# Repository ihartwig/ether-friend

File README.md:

# ether-friend
Custom-purpose and hackable ethernet adapters

[papoe-pi-zero](papoe-pi-zero) Pi Zero HAT with FRC-compatible passive PoE 100M usb-ethernet adapter

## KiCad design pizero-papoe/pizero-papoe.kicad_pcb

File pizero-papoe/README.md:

Pi Zero PaPoE HAT
=================

1GBASE-T ethernet HAT for Pi Zero v1.3, Zero W v 1.1, and Zero 2W using the RTL8153B controller. Also includes a USB C plug to carry USB 3 signals.

### Examples of RTL8153/RTL8153B Implementation
Since the reference schematic from Realtek is not generally available for the RTL8153 part and there are somefeatures requiring specific external components such as the switch regulator, this design borrows from the following schematics:
https://dn.odroid.com/5422/ODROID-XU3/Schematics/XU4_MAIN_REV0.1.pdf
https://www.96boards.org/documentation/consumer/dragonboard/db4/hardware-docs/files/db4-sch.pdf
https://github.com/OLIMEX/USB-GIGABIT/blob/master/HARDWARE/USB-GIGABIT-Rev.C/USB-GIGABIT_Rev_C.pdf

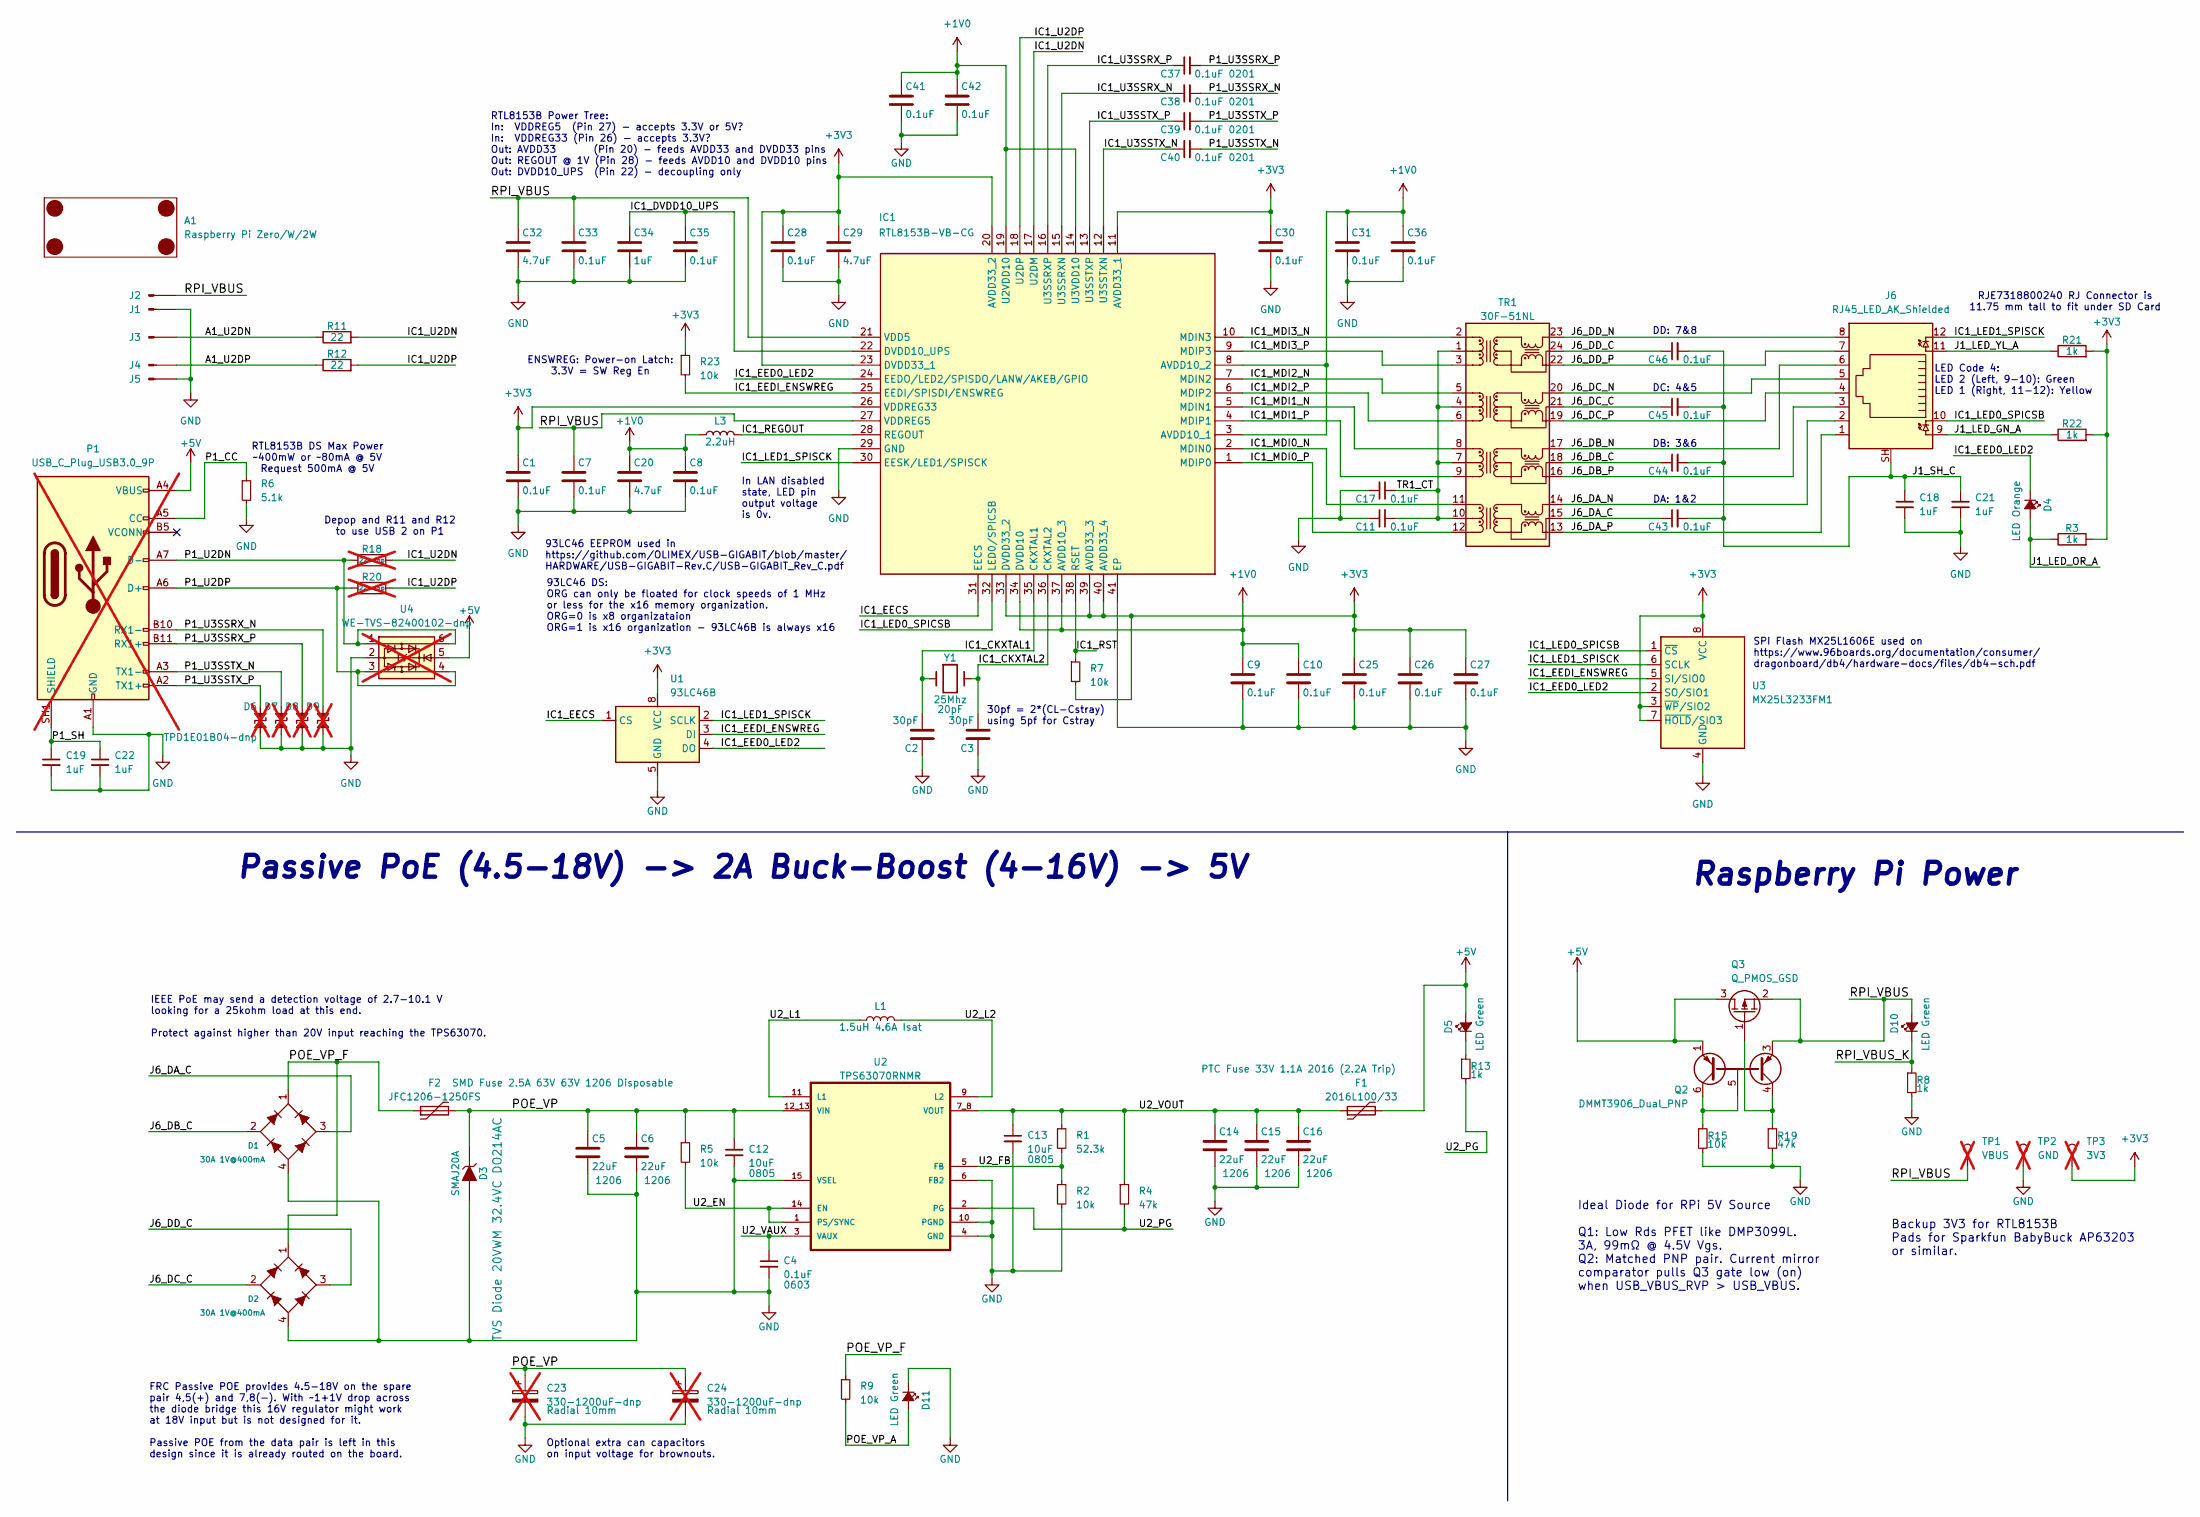
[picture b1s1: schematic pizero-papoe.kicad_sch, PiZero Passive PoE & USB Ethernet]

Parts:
A1: Raspberry Pi Zero/W/2W; RPi_Zero_ZeroW_Zero2W_Hat_NoPads_NoHeader; LCSC --
C1, C7, C8, C9, C10, C11, C17, C25, C26, C27, C28, C30, C31, C33, C35, C36, C41, C42, C43, C44, C45, C46: 0.1uF; C_0603_1608Metric; LCSC C6119867
C2: 30pF; C_0603_1608Metric; Mfg PN 0603CG300F500NT; LCSC C501847
C3: 30pF; C_0603_1608Metric; LCSC C501847
C4: 0.1uF; C_0603_1608Metric; Mfg Part No CC0603KRX7R7BB104; LCSC C6119867
C5: 22uF; C_1206_3216Metric; Mfg Part No CC1206KKX5R8BB226; LCSC C6119965
C6, C14, C15, C16: 22uF; C_1206_3216Metric; LCSC C6119965
C12: 10uF; C_0805_2012Metric; Mfg Part No GRT21BC71E106KE13L; LCSC C882505
C13: 10uF; C_0805_2012Metric; LCSC C882505
C18, C19, C21, C22, C34: 1uF; C_0603_1608Metric; LCSC C5673
C20, C29, C32: 4.7uF; C_0603_1608Metric; LCSC C6119855
C23, C24: 330-1200uF-dnp; CP_Radial_D10.0mm_P5.00mm; Mfg Part No RNL1E122MDSASQ; not fitted
C37, C38, C39, C40: 0.1uF 0201; C_0201_0603Metric; LCSC C6119757
D1: 30A 1V@400mA; MBS; Mfg Part No HD01-T; Digikey Part No HD01DICT-ND
D2: 30A 1V@400mA; MBS; LCSC C2488
D3: SMAJ20A; D_SMA; Mfg Part No SMAJ20A; LCSC C115250
D4: LED Orange; LED_0603_1608Metric; Mfg Part No LTST-C190KFKT; LCSC C157740
D5, D10, D11: LED Green; LED_0603_1608Metric; Mfg Part No LTST-C190GKT; LCSC C125093
D6: TPD1E01B04-dnp; D_0402_1005Metric; Mfg PN TPD1E01B04DPYR; LCSC C779389; not fitted
D7, D8, D9: TPD1E01B04-dnp; D_0402_1005Metric; LCSC C779389; not fitted
F1: 2016L100/33; Fuse_2016_5041Metric; Mfg Part No 2016L100/33DR; LCSC C207077
F2: JFC1206-1250FS; Fuse_1206_3216Metric; Mfg Part No JFC1206-1250FS; LCSC C136346
IC1: RTL8153B-VB-CG; QFN-40-1EP_5x5mm_P0.4mm_EP3.6x3.6mm_ThermalVias; Mfg PN RTL8153B-VB-CG; LCSC C2802072
J1, J2, J3, J4, J5: PogoPin_01x01; PogoPin_CPG-01-TH-TR; Mfg PN CPG-01-TH-B; LCSC --
J6: RJ45_LED_AK_Shielded; RJ45_Amphenol_RJE7318800xxx0x; Mfg PN RJE7318800240; LCSC --
L1: 1.5uH 4.6A Isat; L_Sunlord_SWPA4030S; Mfg Part No XFL4020-152ME; LCSC C5127390
L3: 2.2uH; L_1008_2520Metric; Mfg Part No SFE252010S-2R2M-HF; LCSC C2986800
P1: USB_C_Plug_USB3.0_9P; USB_C_Plug_G-Switch_GT-USB-8016A_9P_TopMnt_Horizontal; Mfg PN GT-USB-8016A; not fitted
Q2: DMMT3906_Dual_PNP; SOT-23-6; Mfg Part No DMMT3906-7-F; Digikey Part No DMMT3906-7-FDICT-ND
Q3: Q_PMOS_GSD; SOT-23; Mfg Part No DMP3099L-7; Digikey Part No DMP3099L-7DICT-ND
R1: 52.3k; R_0603_1608Metric; LCSC C23198
R2, R5, R7, R9, R15, R23: 10k; R_0603_1608Metric; LCSC C15401
R3, R8, R13, R21, R22: 1k; R_0603_1608Metric; LCSC C21190
R4, R19: 47k; R_0603_1608Metric; LCSC C25600
R6: 5.1k; R_0603_1608Metric; LCSC C26000
R11, R12: 22; R_0603_1608Metric; LCSC C1203
R18, R20: 22-dnp; R_0603_1608Metric; not fitted
TP1: VBUS; TestPoint_Pad_D1.5mm; not fitted
TP2: GND; TestPoint_Pad_D1.5mm; not fitted
TP3: 3V3; TestPoint_Pad_D1.5mm; not fitted
TR1: 30F-51NL; Transformer_Ethernet_YDS_30F-51NL_SO-24_7.1x15.1mm; LCSC C123168
U1: 93LC46B; SOIC-8_3.9x4.9mm_P1.27mm; Mfg Pn 93LC46B/SN; LCSC C1348804
U2: TPS63070RNMR; VREG_TPS63070RNMR; Mfg Part No TPS63070RNMR; LCSC C109322
U3: MX25L3233FM1; SOP-8_5.28x5.23mm_P1.27mm; Mfg PN MX25L1606EM2I-12G; LCSC C415878
U4: WE-TVS-82400102-dnp; SOT-23-6; not fitted
Y1: 25Mhz; Crystal_SMD_5032-2Pin_5.0x3.2mm; Mfg Part No 445I23D25M00000; Digikey Part No CTX1175CT-ND

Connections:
+1V0: C8.1, C9.1, C10.1, C20.1, C31.1, C36.1, C41.1, C42.1, IC1.3 (AVDD10_1), IC1.8 (AVDD10_2), IC1.14 (U3VDD10), IC1.19 (U2VDD10), IC1.34 (DVDD10), IC1.37 (AVDD10_3), L3.1
+3V3: C1.1, C25.1, C26.1, C27.1, C28.1, C29.1, C30.1, IC1.11 (AVDD33_1), IC1.20 (AVDD33_2), IC1.23 (DVDD33_1), IC1.26 (VDDREG33), IC1.33 (DVDD33_2), IC1.39 (AVDD33_3), IC1.40 (AVDD33_4), R3.2, R7.2, R21.2, R22.2, R23.1, TP3.1, U1.8 (VCC), U3.3 (~WP/SIO2), U3.7 (~HOLD/SIO3), U3.8 (VCC)
+5V: D5.2 (A), F1.2, P1.A4 (VBUS), P1.A9 (VBUS), P1.B4 (VBUS), P1.B9 (VBUS), Q2.1 (E1), Q3.3 (D), U4.5
/A1_U2DN: J3.1, R11.1
/A1_U2DP: J4.1, R12.1
/IC1_CKXTAL1: C2.2, IC1.35 (CKXTAL1), Y1.1
/IC1_CKXTAL2: C3.2, IC1.36 (CKXTAL2), Y1.2
/IC1_DVDD10_UPS: C34.1, C35.1, IC1.22 (DVDD10_UPS)
/IC1_EECS: IC1.31 (EECS), U1.1 (CS)
/IC1_EED0_LED2: D4.1 (K), IC1.24 (EEDO/LED2/SPISDO/LANW/AKEB/GPIO), U1.4 (DO), U3.2 (SO/SIO1)
/IC1_EEDI_ENSWREG: IC1.25 (EEDI/SPISDI/ENSWREG), R23.2, U1.3 (DI), U3.5 (SI/SIO0)
/IC1_LED0_SPICSB: IC1.32 (LED0/SPICSB), J6.10, U3.1 (~CS)
/IC1_LED1_SPISCK: IC1.30 (EESK/LED1/SPISCK), J6.12, U1.2 (SCLK), U3.6 (SCLK)
/IC1_MDI0_N: IC1.2 (MDIN0), TR1.11 (TD4+)
/IC1_MDI0_P: IC1.1 (MDIP0), TR1.12 (TD4-)
/IC1_MDI1_N: IC1.5 (MDIN1), TR1.8 (TD3+)
/IC1_MDI1_P: IC1.4 (MDIP1), TR1.9 (TD3-)
/IC1_MDI2_N: IC1.7 (MDIN2), TR1.5 (TD2+)
/IC1_MDI2_P: IC1.6 (MDIP2), TR1.6 (TD2-)
/IC1_MDI3_N: IC1.10 (MDIN3), TR1.2 (TD1+)
/IC1_MDI3_P: IC1.9 (MDIP3), TR1.3 (TD1-)
/IC1_REGOUT: IC1.28 (REGOUT), L3.2
/IC1_RST: IC1.38 (RSET), R7.1
/IC1_U2DN: IC1.17 (U2DM), R11.2, R18.2
/IC1_U2DP: IC1.18 (U2DP), R12.2, R20.2
/IC1_U3SSRX_N: C38.1, IC1.15 (U3SSRXN)
/IC1_U3SSRX_P: C37.1, IC1.16 (U3SSRXP)
/IC1_U3SSTX_N: C40.1, IC1.12 (U3SSTXN)
/IC1_U3SSTX_P: C39.1, IC1.13 (U3SSTXP)
/J1_LED_GN_A: J6.9, R22.1
/J1_LED_OR_A: D4.2 (A), R3.1
/J1_LED_YL_A: J6.11, R21.1
/J1_SH_C: C18.1, C21.1, C43.2, C44.2, C45.2, C46.2, J6.SH
/J6_DA_C: C43.1, D1.3 (~2), TR1.15 (CT)
/J6_DA_N: J6.2, TR1.14 (MX4+)
/J6_DA_P: J6.1, TR1.13 (MX4-)
/J6_DB_C: C44.1, D1.2 (~1), TR1.18 (CT)
/J6_DB_N: J6.6, TR1.17 (MX3+)
/J6_DB_P: J6.3, TR1.16 (MX3-)
/J6_DC_C: C45.1, D2.2 (~1), TR1.21 (CT)
/J6_DC_N: J6.5, TR1.20 (MX2+)
/J6_DC_P: J6.4, TR1.19 (MX2-)
/J6_DD_C: C46.1, D2.3 (~2), TR1.24 (CT)
/J6_DD_N: J6.8, TR1.23 (MX1+)
/J6_DD_P: J6.7, TR1.22 (MX1-)
/P1_CC: P1.A5 (CC), R6.1
/P1_SH: C19.1, C22.1, P1.SH1 (SHIELD)
/P1_U2DN: P1.A7 (D-), R18.1, U4.1, U4.6
/P1_U2DP: P1.A6 (D+), R20.1, U4.3, U4.4
/P1_U3SSRX_N: C38.2, D9.1 (A1), P1.B10 (RX1-)
/P1_U3SSRX_P: C37.2, D8.1 (A1), P1.B11 (RX1+)
/P1_U3SSTX_N: C40.2, D7.1 (A1), P1.A3 (TX1-)
/P1_U3SSTX_P: C39.2, D6.1 (A1), P1.A2 (TX1+)
/POE_VP: C5.1, C6.1, C12.1, C23.1, C24.1, D3.1 (K), F2.2, R5.1, U2.12_13 (VIN)
/POE_VP_A: D11.2 (A), R9.2
/POE_VP_F: D1.1 (V+), D2.1 (V+), F2.1, R9.1
/RPI_VBUS: C7.1, C32.1, C33.1, D10.2 (A), IC1.21 (VDD5), IC1.27 (VDDREG5), J2.1, Q2.3 (E2), Q3.2 (S), TP1.1
/RPI_VBUS_K: D10.1 (K), R8.1
/TR1_CT: C11.2, C17.2, TR1.1 (CT), TR1.4 (CT), TR1.7 (CT), TR1.10 (CT)
/U2_EN: R5.2, U2.1 (PS/SYNC), U2.14 (EN)
/U2_FB: R1.2, R2.1, U2.5 (FB)
/U2_L1: L1.1, U2.11 (L1)
/U2_L2: L1.2, U2.9 (L2)
/U2_PG: R4.2, R13.2, U2.2 (PG)
/U2_VAUX: C4.1, U2.3 (VAUX)
/U2_VOUT: C13.1, C14.1, C15.1, C16.1, F1.1, R1.1, R4.1, U2.7_8 (VOUT)
GND: C1.2, C2.1, C3.1, C4.2, C5.2, C6.2, C7.2, C8.2, C9.2, C10.2, C11.1, C12.2, C13.2, C14.2, C15.2, C16.2, C17.1, C18.2, C19.2, C20.2, C21.2, C22.2, C23.2, C24.2, C25.2, C26.2, C27.2, C28.2, C29.2, C30.2, C31.2, C32.2, C33.2, C34.2, C35.2, C36.2, C41.2, C42.2, D1.4 (V-), D2.4 (V-), D3.2 (A), D6.2 (A2), D7.2 (A2), D8.2 (A2), D9.2 (A2), D11.1 (K), IC1.29 (GND), IC1.41 (EP), J1.1, J5.1, P1.A1 (GND), P1.A12 (GND), P1.B1 (GND), P1.B12 (GND), R2.2, R6.2, R8.2, R15.2, R19.2, TP2.1, U1.5 (GND), U2.4 (GND), U2.6 (FB2), U2.10 (PGND), U2.15 (VSEL), U3.4 (GND), U4.2
unnamed: D5.1 (K), R13.1
unnamed: Q2.5 (B), Q2.6 (C1), R15.1
unnamed: Q2.4 (C2), Q3.1 (G), R19.1

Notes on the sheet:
DC: 4&5
Depop and R11 and R12 to use USB 2 on P1
RTL8153B Power Tree: In: VDDREG5 (Pin 27) - accepts 3.3V or 5V? In: VDDREG33 (Pin 26) - accepts 3.3V? Out: AVDD33 (Pin 20) - feeds AVDD33 and DVDD33 pins Out: REGOUT @ 1V (Pin 28) - feeds AVDD10 and DVDD10 pins Out: DVDD10_UPS (Pin 22) - decoupling only
IEEE PoE may send a detection voltage of 2.7-10.1 V looking for a 25kohm load at this end. Protect against higher than 20V input reaching the TPS63070.
RTL8153B DS Max Power ~400mW or ~80mA @ 5V Request 500mA @ 5V
RJE7318800240 RJ Connector is 11.75 mm tall to fit under SD Card
ENSWREG: Power-on Latch: 3.3V = SW Reg En
Passive PoE (4.5-18V) -> 2A Buck-Boost (4-16V) -> 5V
In LAN disabled state, LED pin output voltage is 0v.
30pf = 2*(CL-Cstray) using 5pf for Cstray
DD: 7&8
Raspberry Pi Power
SPI Flash MX25L1606E used on https://www.96boards.org/documentation/consumer/ dragonboard/db4/hardware-docs/files/db4-sch.pdf
Ideal Diode for RPi 5V Source Q1: Low Rds PFET like DMP3099L. 3A, 99mΩ @ 4.5V Vgs. Q2: Matched PNP pair. Current mirror comparator pulls Q3 gate low (on) when USB_VBUS_RVP > USB_VBUS.
DA: 1&2
DB: 3&6
93LC46 EEPROM used in https://github.com/OLIMEX/USB-GIGABIT/blob/master/ HARDWARE/USB-GIGABIT-Rev.C/USB-GIGABIT_Rev_C.pdf
Backup 3V3 for RTL8153B Pads for Sparkfun BabyBuck AP63203 or similar.
FRC Passive POE provides 4.5-18V on the spare pair 4,5(+) and 7,8(-). With ~1+1V drop across the diode bridge this 16V regulator might work at 18V input but is not designed for it. Passive POE from the data pair is left in this design since it is already routed on the board.
93LC46 DS: ORG can only be floated for clock speeds of 1 MHz or less for the x16 memory organization. ORG=0 is x8 organizataion ORG=1 is x16 organization - 93LC46B is always x16
Optional extra can capacitors on input voltage for brownouts.
LED Code 4: LED 2 (Left, 9-10): Green LED 1 (Right, 11-12): Yellow

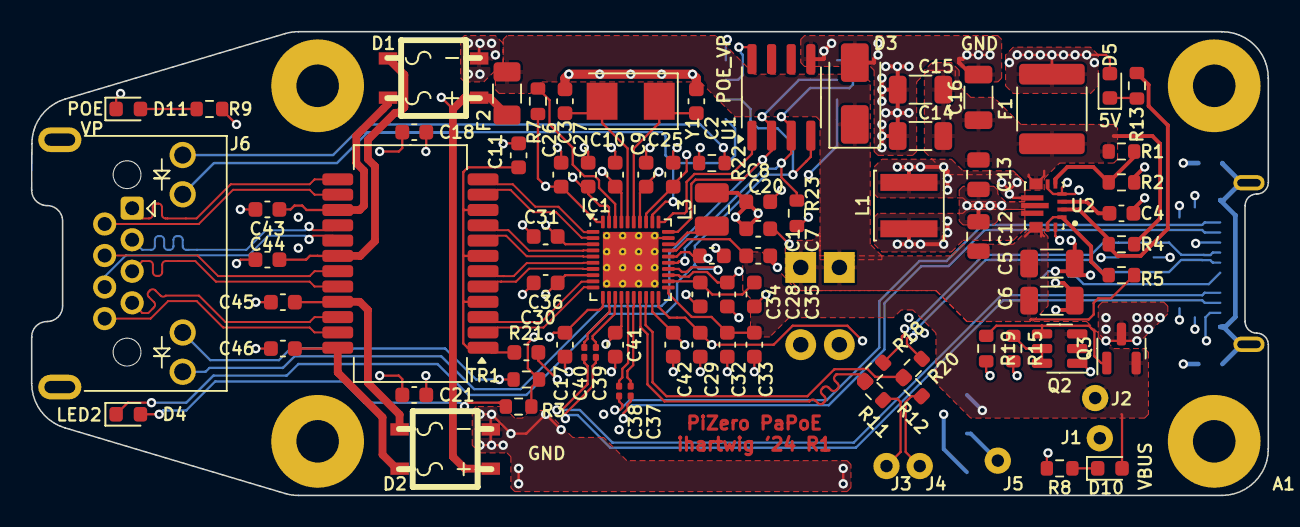
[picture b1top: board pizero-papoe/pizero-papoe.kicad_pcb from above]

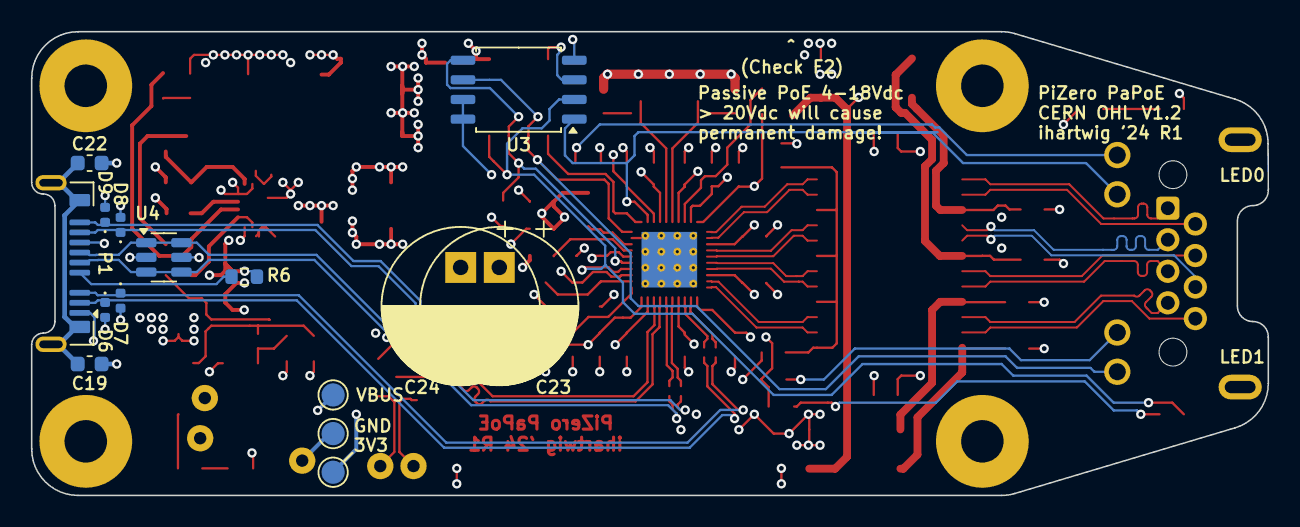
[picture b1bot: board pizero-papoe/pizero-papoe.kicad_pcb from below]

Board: 4 copper layers, 80.0 x 30.0 mm, 100 parts (15 on the bottom side), 70 nets.

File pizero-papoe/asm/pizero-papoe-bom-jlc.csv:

"Designator","Footprint","Qty","DNP","LCSC","Comment","Description"
"A1","Raspberry_Pi_Zero_v.1.3_Hat:RPi_Zero_ZeroW_Zero2W_Hat_NoPads_NoHeader","1","","--","Raspberry Pi Zero/W/2W","Raspberry Pi Zero v1.3"
"C1,C4,C7,C8,C9,C10,C11,C17,C25,C26,C27,C28,C30,C31,C33,C35,C36,C41,C42,C43,C44,C45,C46","Capacitor_SMD:C_0603_1608Metric","23","","C6119867","0.1uF","±10% 100nF 50V X7R 0603 MLCC"
"C2,C3","Capacitor_SMD:C_0603_1608Metric","2","","C501847","30pF",""
"C5,C6,C14,C15,C16","Capacitor_SMD:C_1206_3216Metric","5","","C6119965","22uF","-- mixed values --"
"C12,C13","Capacitor_SMD:C_0805_2012Metric","2","","C882505","10uF","-- mixed values --"
"C18,C19,C21,C22,C34","Capacitor_SMD:C_0603_1608Metric","5","","C5673","1uF","25V 1uF X7R ±10% 0603 MLCC"
"C20,C29,C32","Capacitor_SMD:C_0603_1608Metric","3","","C6119855","4.7uF","16V 4.7uF X5R ±10% 0603 MLCC"
"C37,C38,C39,C40","Capacitor_SMD:C_0201_0603Metric","4","","C6119757","0.1uF 0201","10V 100nF X5R ±10% 0201 MLCC"
"D1,D2","pizero-poe-special:MBS","2","","C2488","30A 1V@400mA","30A 1V@400mA 800mA 100V MBS Bridge Rectifiers ROHS"
"D3","Diode_SMD:D_SMA","1","","C115250","SMAJ20A","TVS Diode 20VWM 32.4VC DO214AC"
"D4","LED_SMD:LED_0603_1608Metric","1","","C157740","LED Orange","LED ORANGE CLEAR 0603 SMD"
"D5,D10,D11","LED_SMD:LED_0603_1608Metric","3","","C125093","LED Green","LED GREEN CLEAR 0603 SMD"
"F1","pizero-poe-special:Fuse_2016_5041Metric","1","","C207077","2016L100/33","PTC Fuse 33V 1.1A 2016 (2.2A Trip)"
"F2","Fuse:Fuse_1206_3216Metric","1","","C136346","JFC1206-1250FS","SMD Fuse 2.5A 63V 63V 1206 Disposable"
"IC1","Package_DFN_QFN:QFN-40-1EP_5x5mm_P0.4mm_EP3.6x3.6mm_ThermalVias","1","","C2802072","RTL8153B-VB-CG",""
"J1,J2,J3,J4,J5","pizero-poe-special:PogoPin_CPG-01-TH-TR","5","","--","PogoPin_01x01",""
"J6","pizero-poe-special:RJ45_Amphenol_RJE7318800xxx0x","1","","--","RJ45_LED_AK_Shielded","RJ connector, 8P8C (8 positions 8 connected), two LEDs, RJ45, Shielded"
"L1","Inductor_SMD:L_Sunlord_SWPA4030S","1","","C5127390","1.5uH 4.6A Isat","1.5uH Shielded inductor ±20% 4.84A SMD,4x4mm Power Inductors ROHS"
"L3","Inductor_SMD:L_1008_2520Metric","1","","C2986800","2.2uH","1.5A 2.2uH ±20% 1.35A 1008 Power Inductors ROHS"
"Q2","Package_TO_SOT_SMD:SOT-23-6","1","","C526572","DMMT3906_Dual_PNP","TRANS 2PNP 40V 0.2A SOT26"
"Q3","Package_TO_SOT_SMD:SOT-23","1","","C155244","Q_PMOS_GSD","MOSFET P-CH 30V SOT23"
"R1","Resistor_SMD:R_0603_1608Metric","1","","C23198","52.3k",""
"R2,R5,R7,R9,R15,R23","Resistor_SMD:R_0603_1608Metric","6","","C15401","10k",""
"R3,R8,R13,R21,R22","Resistor_SMD:R_0603_1608Metric","5","","C21190","1k",""
"R4,R19","Resistor_SMD:R_0603_1608Metric","2","","C25600","47k",""
"R6","Resistor_SMD:R_0603_1608Metric","1","","C26000","5.1k",""
"R11,R12","Resistor_SMD:R_0603_1608Metric","2","","C1203","22",""
"TR1","Transformer_SMD:Transformer_Ethernet_YDS_30F-51NL_SO-24_7.1x15.1mm","1","","C123168","30F-51NL","1CT:1CT 10/100/1000 Base-T Ethernet Transformer, SMD-24"
"U1","Package_SO:SOIC-8_3.9x4.9mm_P1.27mm","1","","C1348804","93LC46B","Serial EEPROM, 93 Series, 2.5V, DIP-8/SOIC-8"
"U2","pizero-poe-special:VREG_TPS63070RNMR","1","","C109322","TPS63070RNMR","Wide input voltage (2V-16V) buck-boost converter"
"U3","Package_SO:SOP-8_5.28x5.23mm_P1.27mm","1","","C415878","MX25L3233FM1","32-Mbit, 3V (2.65V-3.6V) SPI Serial Flash Memory, SOP-8 (150mil)"
"Y1","Crystal:Crystal_SMD_5032-2Pin_5.0x3.2mm","1","","C251592","25Mhz",""

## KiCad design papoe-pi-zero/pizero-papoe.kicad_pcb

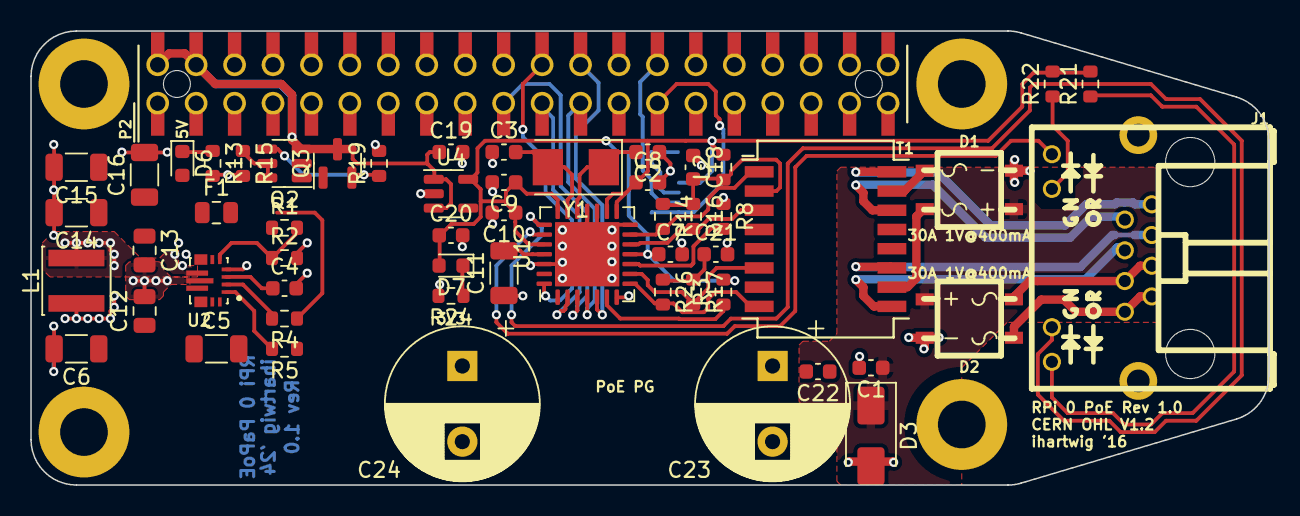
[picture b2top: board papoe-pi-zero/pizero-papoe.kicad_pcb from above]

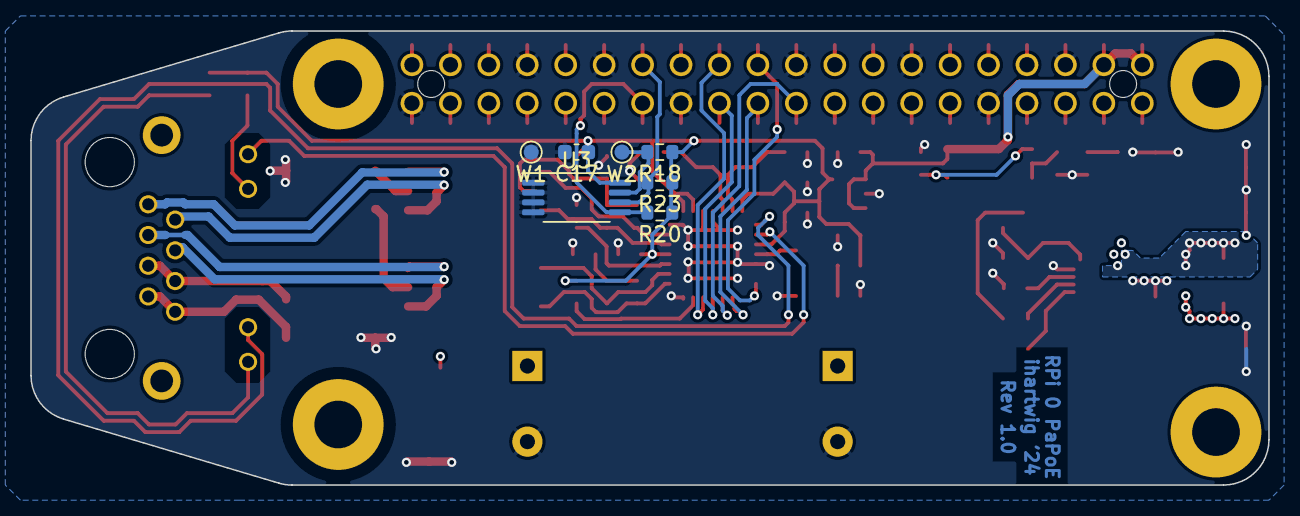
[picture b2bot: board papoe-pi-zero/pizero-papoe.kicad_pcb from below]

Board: 2 copper layers, 81.8 x 30.0 mm, 67 parts (7 on the bottom side), 48 nets.

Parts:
C1, C22: 0.1uf 100V; C_0603_1608Metric
C2, C3: 16pf; C_0603_1608Metric
C4: 0.1uF; C_0603_1608Metric
C5, C6, C14, C15, C16: 22uF; C_1206_3216Metric
C7, C8, C9, C10, C18, C21: 0.1uf; C_0603_1608Metric
C11: 10uf; C_1206_3216Metric
C12, C13: 10uF; C_0805_2012Metric
C17: nostuff-0.1u; C_0603_1608Metric
C19, C20: 1uF; C_0603_1608Metric
C23, C24: nostuff-330-1200uF; CP_Radial_D10.0mm_P5.00mm
D1, D2: 30A 1V@400mA; MBS
D3: SMAJ58A; D_SMA
D6, D7: LED Green; LED_0603_1608Metric
F1: 2016L100/33; Fuse_0805_2012Metric
H1, H2, H3, H4: hole-metalized-no4; hole-m3
J1: RJ45-LED; rj45-tyco-2-406549-7
L1: 1.5uH 4.6A Isat; L_Sunlord_SWPA4030S
L2: BEAD; R_0603_1608Metric
P2: dnp-REF-182665-01; Pin_Header_Straight_TH-SMT-NoPaste_2x20
Q2: DMMT3906_Dual_PNP; SOT-23-6
Q3: Q_PMOS_GSD; SOT-23
R1: 52.3k; R_0603_1608Metric
R2, R5, R15: 10k; R_0603_1608Metric
R3, R13: 1k; R_0603_1608Metric
R4, R19: 47k; R_0603_1608Metric
R8: 2.32k; R_0603_1608Metric
R14, R16, R17, R26: 49.9; R_0603_1608Metric
R18: nostuff-1k; R_0603_1608Metric
R20, R23: nostuff-3.9k; R_0603_1608Metric
R21, R22: 549; R_0603_1608Metric
R24: 220; R_0603_1608Metric
T1: H2019FNL; Transformer_Pulse_H2019FNL
U1: ENC28J60-I/ML; QFN-28-1EP_6x6mm_P0.65mm_EP4.25x4.25mm
U2: TPS63070RNMR; VREG_TPS63070RNMR
U3: nostuff-AT24CS32-SSHM; TSSOP-8_4.4x3mm_P0.65mm
U4: AP7365_SOT-23-5; SOT-23-5
W1, W2: TEST_1P; TestPoint_Pad_D1.0mm
Y1: 25Mhz; Crystal_SMD_5032-2Pin_5.0x3.2mm

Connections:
+3V3: C7.1, C8.1, C9.1, C10.1, C17.1, C20.1, D7.2 (A), L2.2, R3.2, R18.1, R20.1, R21.2, R22.2, R23.1, U1.11 (VDDTX), U1.15 (VDDRX), U1.16 (VDDPLL), U1.21 (VDDOSC), U1.24 (VDD), U3.8 (VCC), U4.5 (VOUT)
+5V: D6.2 (A), F1.2, Q2.1 (E1), Q3.3 (D)
/DATA_PAIR_1: D1.3 (~2), T1.10 (RXCT)
/DATA_PAIR_2: D1.2 (~1), T1.15 (TXCT)
/GPIO0_ID_SD: P2.27, R20.2, U3.5 (SDA)
/GPIO1_ID_SC: P2.28, R23.2, U3.6 (SCL)
/GPIO8_CE0#: P2.24, U1.5 (~CS)
/GPIO9_MISO: P2.21, U1.2 (SO)
/GPIO10_MOSI: P2.19, U1.3 (SI)
/GPIO11_SCLK: P2.23, U1.4 (SCK)
/GPIO25: P2.22, U1.28 (~INT)
/LEDA_A: J1.10 (LED1+), R22.1
/LEDA_K: J1.9 (LED1-), U1.23 (LEDA)
/LEDB_A: J1.12 (LED2+), R21.1
/LEDB_K: J1.11 (LED2-), U1.22 (LEDB)
/PHY_OSC1: C2.2, U1.19 (OSC1), Y1.1
/PHY_OSC2: C3.2, U1.20 (OSC2), Y1.2
/POE_VP: C1.1, C5.1, C6.1, C12.1, C23.1, C24.1, D1.1 (V+), D2.1 (V+), D3.1 (K), R5.1, U2.12_13 (VIN)
/RPI_VBUS: C19.1, P2.2, P2.4, Q2.3 (E2), Q3.2 (S), U4.1 (VIN), U4.3 (EN)
/SPARE_PAIR_1: D2.3 (~2), J1.5, J1.6
/SPARE_PAIR_2: D2.2 (~1), J1.7, J1.8
/TPIN+: R17.2, T1.6 (RD+), U1.9 (TPIN+)
/TPIN-: R26.2, T1.8 (RD-), U1.8 (TPIN-)
/TPIN_T+: J1.3, T1.11 (RX+)
/TPIN_T-: J1.4, T1.9 (RX-)
/TPOUT+: R14.2, T1.1 (TD+), U1.13 (TPOUT+)
/TPOUT-: R16.2, T1.3 (TD-), U1.12 (TPOUT-)
/TPOUT_T+: J1.1, T1.16 (TX+)
/TPOUT_T-: J1.2, T1.14 (TX-)
/U2_EN: R5.2, U2.1 (PS/SYNC), U2.14 (EN)
/U2_FB: R1.2, R2.1, U2.5 (FB)
/U2_L1: L1.1, U2.11 (L1)
/U2_L2: L1.2, U2.9 (L2)
/U2_PG: R4.2, U2.2 (PG)
/U2_VAUX: C4.1, U2.3 (VAUX)
/U2_VOUT: C13.1, C14.1, C15.1, C16.1, F1.1, R1.1, R4.1, U2.7_8 (VOUT)
GND: C2.1, C3.1, C4.2, C5.2, C6.2, C7.2, C8.2, C9.2, C10.2, C11.1, C12.2, C13.2, C14.2, C15.2, C16.2, C17.2, C18.1, C19.2, C20.2, C21.2, C22.2, C23.2, C24.2, D1.4 (V-), D2.4 (V-), D3.2 (A), P2.6, P2.9, P2.14, P2.20, P2.25, P2.30, P2.34, P2.39, R2.2, R8.1, R13.2, R15.2, R19.2, R24.2, U1.7 (VSSRX), U1.14 (VSSTX), U1.17 (VSSPLL), U1.18 (VSSOSC), U1.26 (VSS), U1.29 (PAD), U2.4 (GND), U2.6 (FB2), U2.10 (PGND), U2.15 (VSEL), U3.1 (A0), U3.2 (A1), U3.3 (A2), U3.4 (GND), U4.2 (GND), W1.1
unnamed: C1.2, C22.1
unnamed: C21.1, R17.1, R26.1
unnamed: D6.1 (K), R13.1
unnamed: D7.1 (K), R24.1
unnamed: Q2.5 (B), Q2.6 (C1), R15.1
unnamed: Q2.4 (C2), Q3.1 (G), R19.1
unnamed: C18.2, L2.1, R14.1, R16.1, T1.2 (TDCT)
unnamed: R8.2, U1.10 (RBIAS)
unnamed: C11.2, U1.25 (VCAP)
unnamed: R3.1, U1.6 (~RESET)
unnamed: R18.2, U3.7 (WP), W2.1

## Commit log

2024-12-08 move papoe-pi-zero from PoEPi-hardware/passive-poe-only-top-smt
2024-12-08 update readme gitignore
2024-12-08 papoe-pi-zero -> pizero-papoe
2024-12-22 sch updates for RTL8153B and RJE7318800240
2024-12-27 complete RTL8153B sch
2024-12-30 pcb routing for RTL8153B and RJE7318800240
2024-12-30 add JLC04162H-3313-stackup info
2024-12-31 pizero-papoe sch pcb fixes and cleanup
2024-12-31 pizero-papoe generate gerbers
2025-01-02 pizero-papoe pcb sch bom tweaks for r1
2025-01-21 add pizero-papoe bom info and step export

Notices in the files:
papoe-pi-zero/pizero-papoe.kicad_pcb:
License: CERN OHL V1.2
CERN OHL V1.2
